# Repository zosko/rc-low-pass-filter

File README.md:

Arduino convert from PWM to Voltage. In this example is used Arduino Nano.

Output pin depends on `analogWrite` value give from 0v to 4.5v

## Scheme XIAO

## Kicad XIAO
Board|PCB
----|----
|

## Scheme

## Kicad
Board|PCB filled|PCB
----|----|----
||

## Final

## PCB Design

For PCB design i will use services from SeeedFusion. 

Seeed Fusion PCB Assembly Service offers one-stop prototyping for PCB manufacture, PCB assembly and as a result they produce superior quality PCBs and Fast Turnkey PCBA from 7 working days. When you prototype with Seeed Fusion, they can definitely provide Free DFA and Free functional tests for you! 

Check out their website to know about their manufacturing capabilities and service.
https://www.seeedstudio.com/pcb-assembly.html

## Reasons to choose Seeed Studio
- They provide PCB services at extremely low pricing and with excellent quality.
- Their offer is structured in such a way that everyone may have these boards at a reasonable price.
- They have a highly knowledgeable crew that leads their clients to avail deals and guides them about the costs and rates of different services.
- A four-layer board with a comparable feature costs $5 for 10 pieces and is made in four days.
- SMT stencil with size (10cm x 13cm) is available for $8.00 per piece.

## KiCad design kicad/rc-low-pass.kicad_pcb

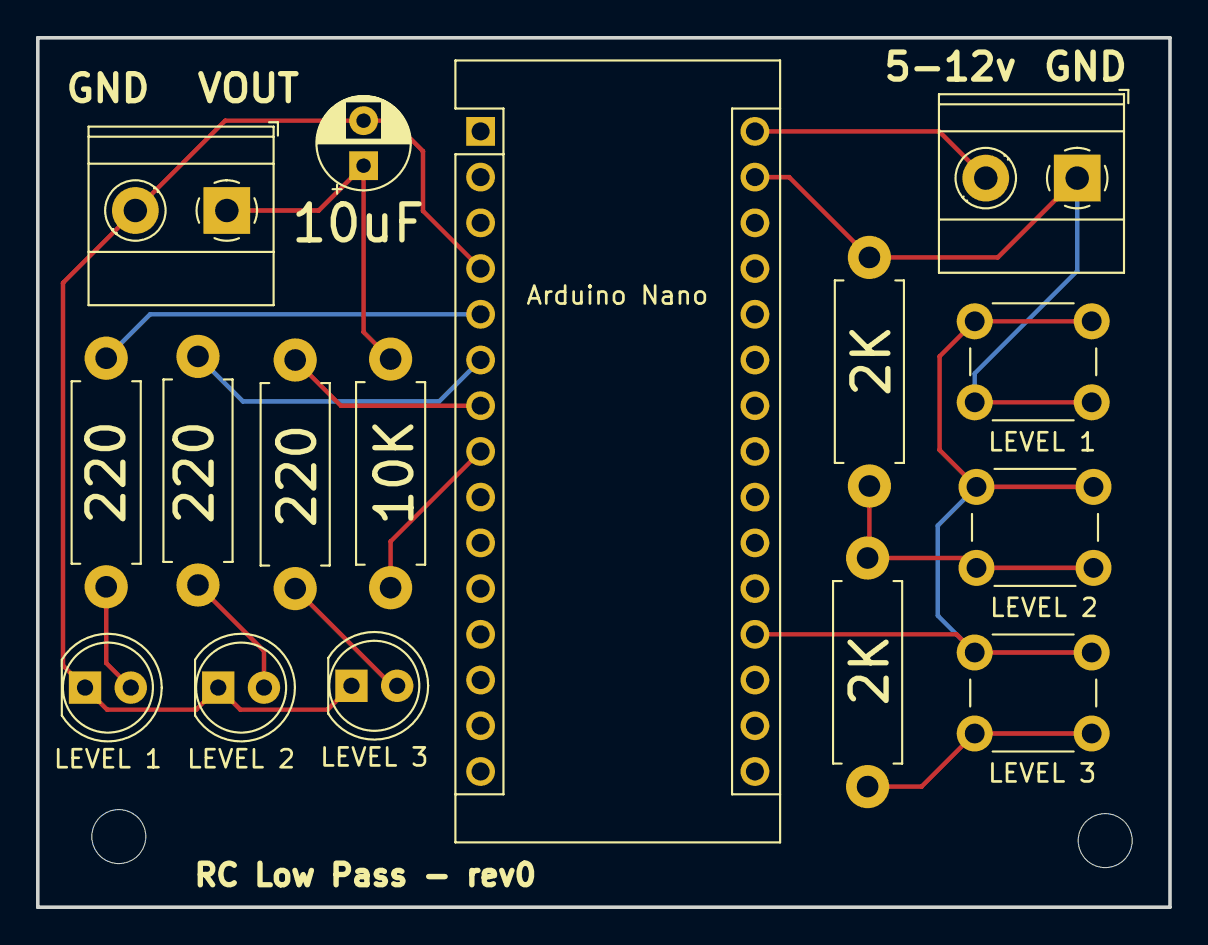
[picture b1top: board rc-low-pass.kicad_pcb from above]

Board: 2 copper layers, 62.9 x 48.3 mm, 18 parts (0 on the bottom side), 14 nets.

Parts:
2K, 2K#2: 2K; R_Axial_DIN0411_L9.9mm_D3.6mm_P12.70mm_Horizontal
A1: Arduino Nano; Arduino_Nano
C1: 10uF; CP_Radial_D5.0mm_P2.50mm
D1: LEVEL 1; LED_D5.0mm
D2: LEVEL 2; LED_D5.0mm
D3: LEVEL 3; LED_D5.0mm
H1, H2: MountingHole; MountingHole_3mm
J1: Out; TerminalBlock_Phoenix_MKDS-1,5-2-5.08_1x02_P5.08mm_Horizont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
J2: In; TerminalBlock_Phoenix_MKDS-1,5-2-5.08_1x02_P5.08mm_Horizont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
R1: 10K; R_Axial_DIN0411_L9.9mm_D3.6mm_P12.70mm_Horizontal
R4, R5, R6: 220; R_Axial_DIN0411_L9.9mm_D3.6mm_P12.70mm_Horizontal
SW1: LEVEL 1; SW_PUSH_6mm
SW2: LEVEL 2; SW_PUSH_6mm
SW3: LEVEL 3; SW_PUSH_6mm

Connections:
ANALOG: A1.19 (A0), SW1.1, SW2.1, SW3.1
ARDUINO_PIN: A1.8 (D5), R1.1
GND: A1.4 (GND), C1.2, D1.1 (K), D2.1 (K), D3.1 (K), J1.2
GND1: 2K#2.2, A1.29 (GND), J2.1, SW1.2
LED_1: A1.5 (D2), R4.1
LED_2: A1.6 (D3), R5.1
LED_3: A1.7 (D4), R6.1
unnamed: 2K.1, SW3.2
unnamed: 2K.2, 2K#2.1, SW2.2
unnamed: D1.2 (A), R4.2
unnamed: D2.2 (A), R5.2
unnamed: D3.2 (A), R6.2
VOLTAGE_IN: A1.30 (VIN), J2.2
VOLTAGE_OUT: C1.1, J1.1, R1.2

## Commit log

2022-02-26 add input voltage
2022-02-27 add led indicators of levels
2022-04-01 code update
2023-03-11 add XIAO variation
